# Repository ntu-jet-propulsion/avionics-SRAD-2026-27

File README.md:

TLB_Questions

Question 01:
+5V isolated copper: KiCad is still showing an “isolated copper fill” warning for the +5V zone on In1.Cu. Is this okay to leave, or should I modify/remove the isolated +5V region?

Question 02:
SDA connection: KiCad shows a “copper connection too narrow” warning on the SDA connection, with an effective width of ~0.041 mm even though the track itself is 0.25 mm. Is this something I need to fix, or can it be ignored?

Question 03:
GND vias near J1/J2: KiCad shows drilled-hole clearance warnings because some GND vias are extremely close to the J1/J2 connector PTH holes. Should I move these vias, or is the current placement acceptable?

Question 04:
ESP32 footprint: KiCad reports that the ESP32-C3-WROOM-02 footprint doesn't match the current library footprint. We used the existing/different footprint for the board — is this intentional and okay to keep?

Question 05:
Silkscreen warnings: There are several silkscreen clearance/clipping warnings. Do I need to clean these up before fabrication, or are they acceptable?

Question 06:
Mounting holes: I added two 5 mm NPTH mounting holes. Is their current placement acceptable?

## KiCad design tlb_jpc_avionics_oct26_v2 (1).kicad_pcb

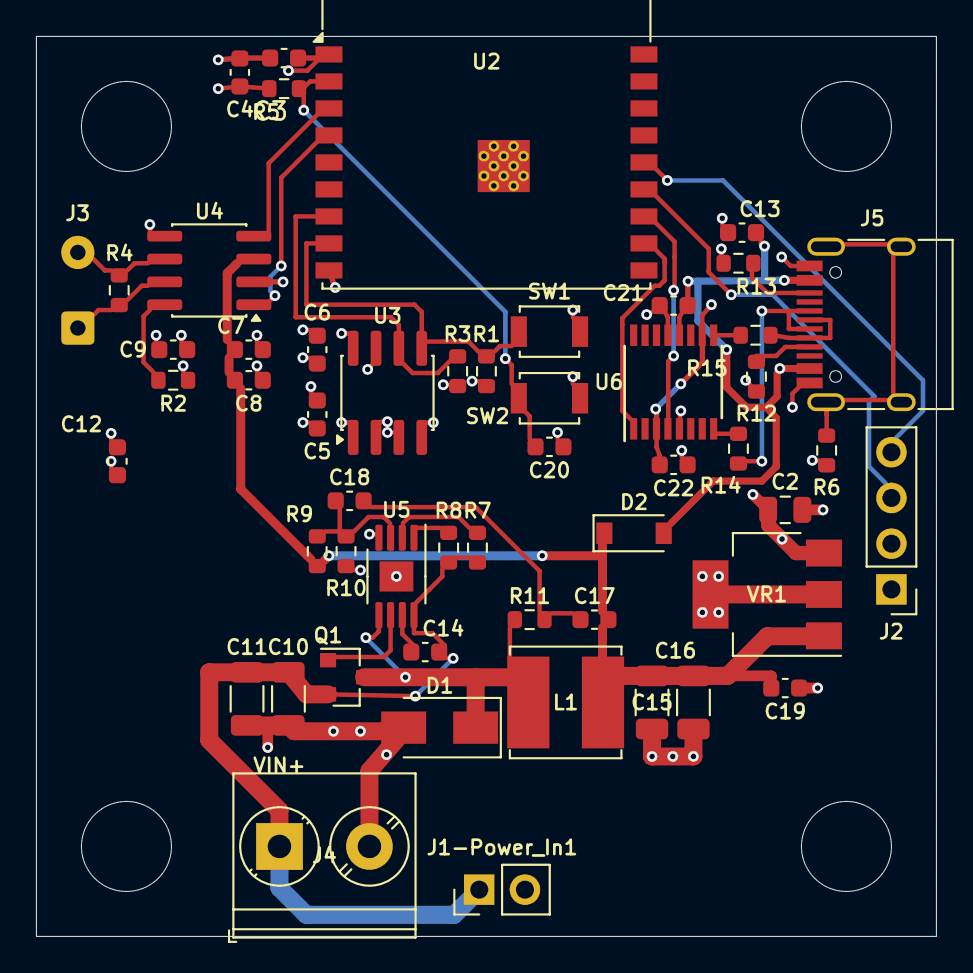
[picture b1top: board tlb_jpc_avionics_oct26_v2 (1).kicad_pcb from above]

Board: 4 copper layers, 50.0 x 50.0 mm, 57 parts (0 on the bottom side), 32 nets.

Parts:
C2: 33u; C_0805_2012Metric
C3, C5, C6, C8, C12: 0.1 uF; C_0603_1608Metric
C4: 10uF; C_0603_1608Metric
C7, C9, C13, C21, C22: 0.1uF; C_0603_1608Metric
C10, C11: 4.7uF 50V; C_1206_3216Metric
C14: 0.47uF 50V; C_0603_1608Metric
C15, C16: 22uF 10V; C_1206_3216Metric
C17: CR (ripple); C_0603_1608Metric
C18: CAC (ripple); C_0603_1608Metric
C19: 0.47uF; C_0603_1608Metric
C20: 1uF; C_0603_1608Metric
D1: SS34 Schottky; D_SMA
D2: B5819W; D_SOD-123
H1, H2, H3, H4: MountingHole_5mm_NPTH; MountingHole_5mm
J1-Power_In1: Conn_01x02; PinHeader_1x02_P2.54mm_Vertical
J2: Light_APRS; PinHeader_1x04_P2.54mm_Vertical
J3: CAN (H,L); SolderWire-0.25sqmm_1x02_P4.2mm_D0.65mm_OD1.7mm
J4: PT1.5/2-5.0-H VIN; TerminalBlock_Phoenix_PT-1,5-2-5.0-H_1x02_P5.00mm_Horizontal
J5: USB-C (HRO TYPE-C-31-M-12); USB_C_Receptacle_HRO_TYPE-C-31-M-12
L1: 15uH SRN6045TA; L_Bourns_SRN6045TA
Q1: PFET -30V (AO3401A); SOT-23-3
R1, R3: 4.7k; R_0603_1608Metric
R2, R5: 10kR; R_0603_1608Metric
R4: 120R; R_0603_1608Metric
R6: 0; R_0603_1608Metric
R7: RT; R_0603_1608Metric
R8: RADJ; R_0603_1608Metric
R9: 3.01k; R_0603_1608Metric
R10: 1.00k; R_0603_1608Metric
R11: RR (ripple); R_0603_1608Metric
R12, R13: 5.1k; R_0603_1608Metric
R14, R15: 27R; R_0603_1608Metric
SW1: BOOT (IO9); SW_SPST_B3U-1000P
SW2: RESET (EN); SW_SPST_B3U-1000P
U2: ESP32-C3; ESP32-C3-WROOM-02
U3: 24LC256; SOIC-8_3.9x4.9mm_P1.27mm
U4: TJA1051TK-3; SOIC-8_3.9x4.9mm_P1.27mm
U5: LM25085MY; MSOP-8-1EP_3x3mm_P0.65mm_EP1.68x1.88mm
U6: FT230XS; SSOP-16_3.9x4.9mm_P0.635mm
VR1: LM3940IMP-3.3; SOT-223-3_TabPin2

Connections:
+3V3: C2.1, C3.2, C4.1, C5.1, C6.1, C9.1, J2.1, R1.1, R3.1, R5.1, U2.1 (3V3), U3.8 (VCC), U4.5 (VIO), VR1.3
+5V: C7.1, C8.2, C15.1, C16.1, C17.2, C19.1, D2.1, L1.2, R9.1, U4.3 (VCC), VR1.1
/APRS_RX: J2.4, U2.14 (IO19)
/APRS_TX: J2.3, U2.13 (IO18)
/BUCK_ADJ: R8.2, U5.1
/BUCK_FB: C18.1, R9.2, R10.2, U5.3
/BUCK_PGATE: Q1.1, U5.6
/BUCK_RIP: C17.1, C18.2, R11.2
/BUCK_RT: R7.2, U5.2
/BUCK_SW: D1.1, L1.1, Q1.3, R11.1, U5.5
/BUCK_VCC: C14.1, U5.7
/CANH: J3.1, R4.1, U4.7 (CANH)
/CANL: J3.2, R4.2, U4.6 (CANL)
/CANRX: U2.3 (IO4), U4.4 (RXD)
/CANTX: U2.4 (IO5), U4.1 (TXD)
/CC1: J5.A5, R12.2
/CC2: J5.B5, R13.2
/FT_3V3: C22.1, U6.3, U6.10
/FT_DM: R15.1, U6.9
/FT_DP: R14.2, U6.8
/SCL: R3.2, U2.7 (IO8), U3.6 (SCL)
/SDA: R1.2, SW1.1, U2.8 (IO9), U3.5 (SDA)
/U0RXD: U2.11 (IO20/RXD), U6.1
/U0TXD: U2.12 (IO21/TXD), U6.4
D+: J5.A6, J5.B6, R14.1
D-: J5.A7, J5.B7, R15.2
GND: C2.2, C3.1, C4.2, C5.2, C6.2, C7.2, C8.1, C9.2, C10.2, C11.2, C12.1, C12.2, C13.1, C15.2, C16.2, C19.2, C20.2, C21.2, C22.2, D1.2, J1-Power_In1.2, J2.2, J4.2, J5.A1, J5.A12, J5.B1, J5.B12, R2.2, R6.2, R10.1, R12.1, R13.1, SW1.2, SW2.2, U2.9 (GND), U2.19 (GND), U3.1 (A0), U3.2 (A1), U3.3 (A2), U3.4 (GND), U3.7 (WP), U4.2 (GND), U5.4, U5.9, U6.5, U6.13, VR1.2
unnamed: J5.S1, R6.1
unnamed: C13.2, C21.1, D2.2, J5.A4, J5.A9, J5.B4, J5.B9, U6.12
unnamed: C20.1, R5.2, SW2.1, U2.2 (EN)
unnamed: R2.1, U4.8 (S)
VIN: C10.1, C11.1, C14.2, J1-Power_In1.1, J4.1, Q1.2, R7.1, R8.1, U5.8

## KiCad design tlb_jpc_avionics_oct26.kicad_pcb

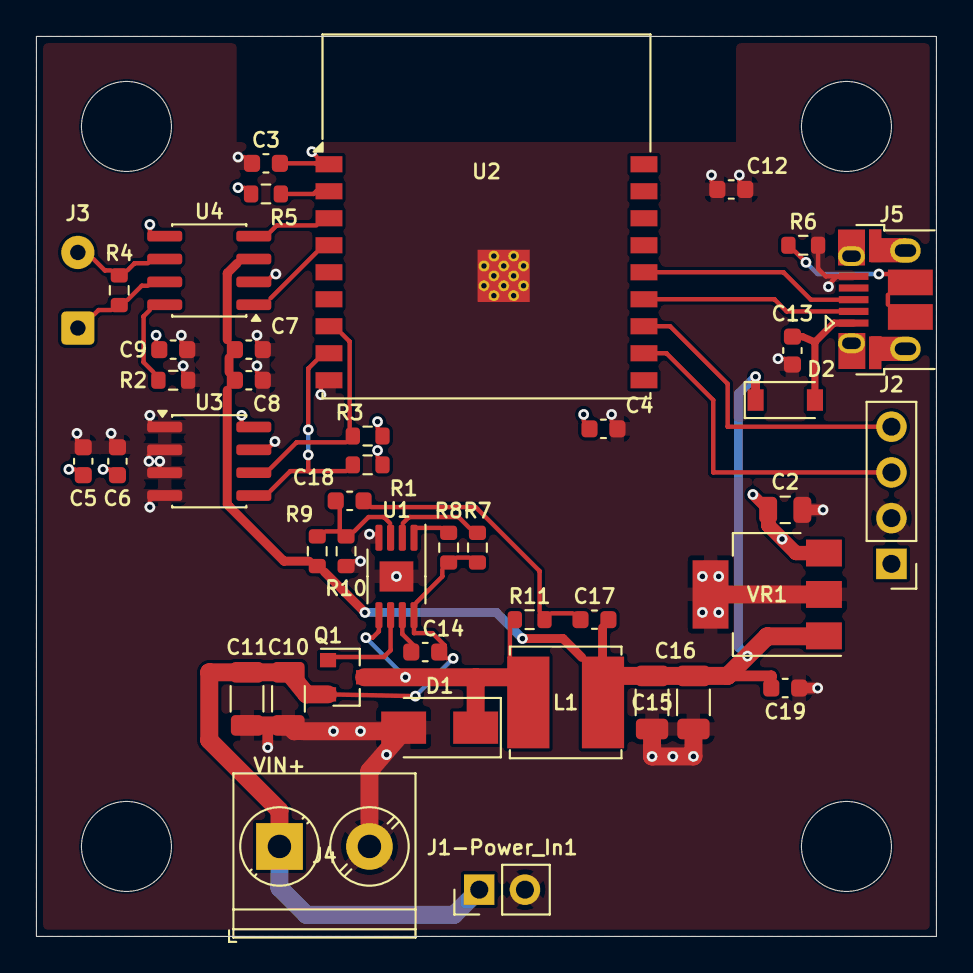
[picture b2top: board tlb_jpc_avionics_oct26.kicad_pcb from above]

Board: 4 copper layers, 50.0 x 50.0 mm, 47 parts (0 on the bottom side), 25 nets.

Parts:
C2: 33u; C_0805_2012Metric
C3, C4, C5, C6, C8, C12: 0.1 uF; C_0603_1608Metric
C7, C9, C13: 0.1uF; C_0603_1608Metric
C10, C11: 4.7uF 50V; C_1206_3216Metric
C14: 0.47uF 50V; C_0603_1608Metric
C15, C16: 22uF 10V; C_1206_3216Metric
C17: CR (ripple); C_0603_1608Metric
C18: CAC (ripple); C_0603_1608Metric
C19: 0.47uF; C_0603_1608Metric
D1: SS34 Schottky; D_SMA
D2: B5819W; D_SOD-123
H1, H2, H3, H4: MountingHole_5mm_NPTH; MountingHole_5mm
J1-Power_In1: Conn_01x02; PinHeader_1x02_P2.54mm_Vertical
J2: Light_APRS; PinHeader_1x04_P2.54mm_Vertical
J3: CAN (H,L); SolderWire-0.25sqmm_1x02_P4.2mm_D0.65mm_OD1.7mm
J4: PT1.5/2-5.0-H VIN; TerminalBlock_Phoenix_PT-1,5-2-5.0-H_1x02_P5.00mm_Horizontal
J5: USB_B_Micro; USB_Micro-B_Amphenol_10103594-0001LF_Horizontal
L1: 15uH SRN6045TA; L_Bourns_SRN6045TA
Q1: PFET -30V (AO3401A); SOT-23-3
R1, R3: 4.7k; R_0603_1608Metric
R2, R5: 10kR; R_0603_1608Metric
R4: 120R; R_0603_1608Metric
R6: 0; R_0603_1608Metric
R7: RT; R_0603_1608Metric
R8: RADJ; R_0603_1608Metric
R9: 3.01k; R_0603_1608Metric
R10: 1.00k; R_0603_1608Metric
R11: RR (ripple); R_0603_1608Metric
U1: LM25085MY; MSOP-8-1EP_3x3mm_P0.65mm_EP1.68x1.88mm
U2: ESP32-C3; ESP32-C3-WROOM-02
U3: 24LC256; SOIC-8_3.9x4.9mm_P1.27mm
U4: TJA1051TK-3; SOIC-8_3.9x4.9mm_P1.27mm
VR1: LM3940IMP-3.3; SOT-223-3_TabPin2

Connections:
+3V3: C2.1, C3.2, C4.1, C5.1, C6.1, C9.1, J2.1, R1.1, R3.1, R5.1, U2.1 (3V3), U3.8 (VCC), U4.5 (VIO), VR1.3
+5V: C7.1, C8.2, C15.1, C16.1, C17.2, C19.1, D2.1, L1.2, R9.1, U4.3 (VCC), VR1.1
/BUCK_ADJ: R8.2, U1.1
/BUCK_FB: C18.1, R9.2, R10.2, U1.3
/BUCK_PGATE: Q1.1, U1.6
/BUCK_RIP: C17.1, C18.2, R11.2
/BUCK_RT: R7.2, U1.2
/BUCK_SW: D1.1, L1.1, Q1.3, R11.1, U1.5
/BUCK_VCC: C14.1, U1.7
/CANH: J3.1, R4.1, U4.7 (CANH)
/CANL: J3.2, R4.2, U4.6 (CANL)
/CANRX: U2.3 (IO4), U4.4 (RXD)
/CANTX: U2.4 (IO5), U4.1 (TXD)
/RX0: J2.4, U2.12 (IO21/TXD)
/SCL: R3.2, U2.7 (IO8), U3.6 (SCL)
/SDA: R1.2, U2.8 (IO9), U3.5 (SDA)
/TX0: J2.3, U2.11 (IO20/RXD)
D+: J5.3 (D+), U2.14 (IO19)
D-: J5.2 (D-), U2.13 (IO18)
GND: C2.2, C3.1, C4.2, C5.2, C6.2, C7.2, C8.1, C9.2, C10.2, C11.2, C12.1, C12.2, C13.1, C15.2, C16.2, C19.2, D1.2, J1-Power_In1.2, J2.2, J4.2, J5.5 (GND), R2.2, R6.2, R10.1, U1.4, U1.9, U2.9 (GND), U2.19 (GND), U3.1 (A0), U3.2 (A1), U3.3 (A2), U3.4 (GND), U3.7 (WP), U4.2 (GND), VR1.2
unnamed: J5.6 (Shield), R6.1
unnamed: C13.2, D2.2, J5.1 (VBUS)
unnamed: R5.2, U2.2 (EN)
unnamed: R2.1, U4.8 (S)
VIN: C10.1, C11.1, C14.2, J1-Power_In1.1, J4.1, Q1.2, R7.1, R8.1, U1.8

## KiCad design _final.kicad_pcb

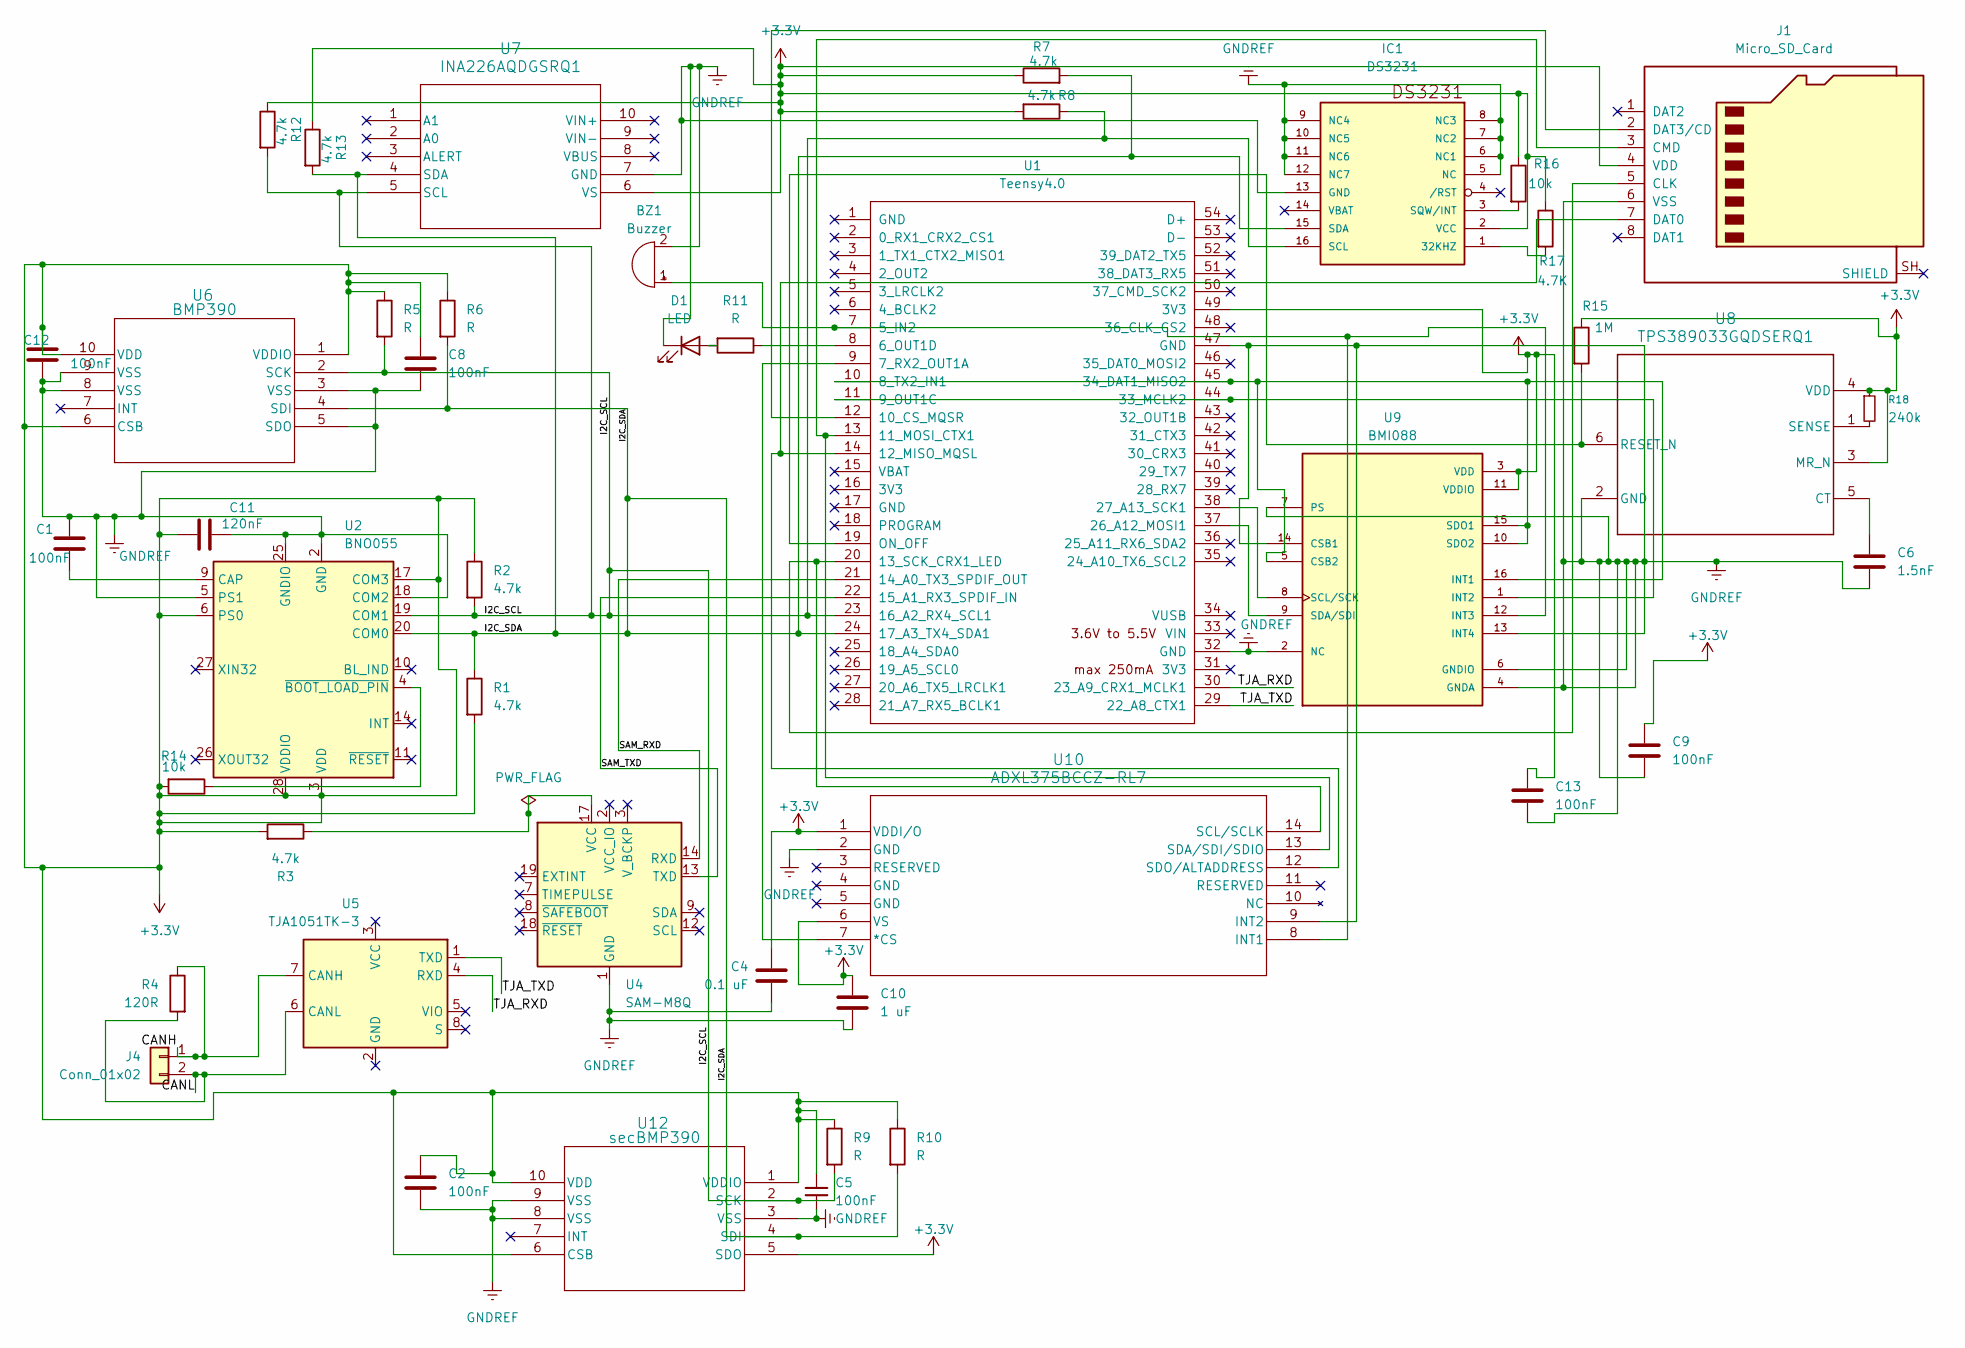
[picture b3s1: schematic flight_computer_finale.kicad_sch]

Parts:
BZ1: Buzzer; Buzzer_12x9.5RM7.6
C1, C2, C5, C8, C9, C12, C13: 100nF; C_01005_0402Metric
C4: 0.1 uF; C_01005_0402Metric
C6: 1.5nF; C_01005_0402Metric
C10: 1 uF; C_01005_0402Metric
C11: 120nF; C_01005_0402Metric
D1: LED; LED_0201_0603Metric
IC1: DS3231; 21-0042B_16_MXM
J1: Micro_SD_Card; microSD_HC_Wuerth_693072010801
J4: Conn_01x02; PinHeader_1x02_P2.54mm_Vertical
R1, R2, R3, R7, R8, R12, R13: 4.7k; R_01005_0402Metric
R4: 120R; R_01005_0402Metric
R5, R6, R9, R10, R11: R; R_01005_0402Metric
R14, R16: 10k; R_01005_0402Metric
R15: 1M; R_01005_0402Metric
R17: 4.7K; R_01005_0402Metric
R18: 240k; R_01005_0402Metric
U1: Teensy4.0; Teensy40_SMT
U2: BNO055; LGA-28_5.2x3.8mm_P0.5mm
U4: SAM-M8Q; ublox_SAM-M8Q
U5: TJA1051TK-3; HVSON-8-1EP_3x3mm_P0.65mm_EP1.6x2.4mm
U6: BMP390; 10LGA_2X2X0p75_BOS
U7: INA226AQDGSRQ1; DGS10_TEX
U8: TPS389033GQDSERQ1; DSE0006A
U9: BMI088; QFN_BMI085_BOS
U10: ADXL375BCCZ-RL7; LGA_CC-14-1_ADI
U12: secBMP390; 10LGA_2X2X0p75_BOS

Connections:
+3.3V: C2.1, C4.1, C5.1, C8.1, C9.1, C10.1, C11.1, C12.1, C13.1, IC1.2 (VCC), J1.4 (VDD), R1.2, R2.1, R3.2, R5.1, R6.1, R7.1, R8.2, R9.1, R10.1, R12.1, R13.1, R14.2, R15.1, R16.1, R17.1, R18.1, U1.49 (3V3), U2.3 (VDD), U2.6 (PS0), U2.17 (COM3), U2.28 (VDDIO), U6.1 (VDDIO), U6.6 (CSB), U6.10 (VDD), U7.6 (VS), U8.3 (MR_N), U8.4 (VDD), U9.3 (VDD), U9.11 (VDDIO), U10.1 (VDDI/O), U10.6 (VS), U12.1 (VDDIO), U12.5 (SDO), U12.6 (CSB), U12.10 (VDD)
/CANH: J4.1, R4.1, U5.7 (CANH)
/CANL: J4.2, R4.2, U5.6 (CANL)
/I2C_SCL: IC1.16 (SCL), R2.2, R5.2, R8.1, R9.2, R12.2, U1.23 (16_A2_RX4_SCL1), U2.19 (COM1), U6.2 (SCK), U7.5 (SCL), U12.2 (SCK)
/I2C_SDA: IC1.15 (SDA), R1.1, R6.2, R7.2, R10.2, R13.2, U1.24 (17_A3_TX4_SDA1), U2.20 (COM0), U6.4 (SDI), U7.4 (SDA), U12.4 (SDI)
/SAM_RXD: U1.21 (14_A0_TX3_SPDIF_OUT), U4.14 (RXD)
/SAM_TXD: U1.22 (15_A1_RX3_SPDIF_IN), U4.13 (TXD)
/TJA_RXD: U1.30 (23_A9_CRX1_MCLK1), U5.4 (RXD)
/TJA_TXD: U1.29 (22_A8_CTX1), U5.1 (TXD)
GNDREF: BZ1.2 (-), C1.1, C2.2, C4.2, C5.2, C6.2, C8.2, C9.2, C10.2, C11.2, C12.2, C13.2, D1.1 (K), IC1.5 (NC), IC1.6 (NC1), IC1.7 (NC2), IC1.8 (NC3), IC1.9 (NC4), IC1.10 (NC5), IC1.11 (NC6), IC1.12 (NC7), IC1.13 (GND), J1.6 (VSS), U1.32 (GND), U1.47 (GND), U2.2 (GND), U2.5 (PS1), U2.18 (COM2), U2.25 (GNDIO), U4.1 (GND), U4.4 (GND), U4.5 (GND), U4.6 (GND), U4.10 (GND), U4.11 (GND), U4.15 (GND), U4.16 (GND), U4.20 (GND), U6.3 (VSS), U6.5 (SDO), U6.8 (VSS), U6.9 (VSS), U7.7 (GND), U8.2 (GND), U9.2 (NC), U9.4 (GNDA), U9.6 (GNDIO), U9.7 (PS), U9.13 (INT4), U9.14 (CSB1), U10.2 (GND), U10.9 (INT2), U12.3 (VSS), U12.8 (VSS), U12.9 (VSS)
unnamed: BZ1.1 (+), U1.7 (5_IN2), U9.12 (INT3), U10.8 (INT1)
unnamed: D1.2 (A), R11.2
unnamed: IC1.1 (32KHZ), R17.2
unnamed: IC1.3 (SQW/INT), R16.2
unnamed: J1.5 (CLK), U1.20 (13_SCK_CRX1_LED), U10.14 (SCL/SCLK)
unnamed: J1.3 (CMD), U1.13 (11_MOSI_CTX1), U10.13 (SDA/SDI/SDIO)
unnamed: J1.7 (DAT0), U1.14 (12_MISO_MQSL), U10.12 (SDO/ALTADDRESS)
unnamed: J1.2 (DAT3/CD), U1.12 (10_CS_MQSR)
unnamed: R11.1, U1.8 (6_OUT1D)
unnamed: U1.9 (7_RX2_OUT1A), U10.7 (*CS)
unnamed: U1.37 (26_A12_MOSI1), U9.9 (SDA/SDI)
unnamed: U1.38 (27_A13_SCK1), U9.8 (SCL/SCK)
unnamed: U1.11 (9_OUT1C), U1.44 (33_MCLK2), U9.1 (INT2)
unnamed: U1.10 (8_TX2_IN1), U1.45 (34_DAT1_MISO2), U9.5 (CSB2), U9.10 (SDO2), U9.15 (SDO1), U9.16 (INT1)
unnamed: R15.2, U1.19 (ON_OFF), U8.6 (RESET_N)
unnamed: C1.2, U2.9 (CAP)
unnamed: R14.1, U2.4 (~BOOT_LOAD_PIN)
unnamed: R3.1, U4.17 (VCC)
unnamed: C6.1, U8.5 (CT)
unnamed: R18.2, U8.1 (SENSE)

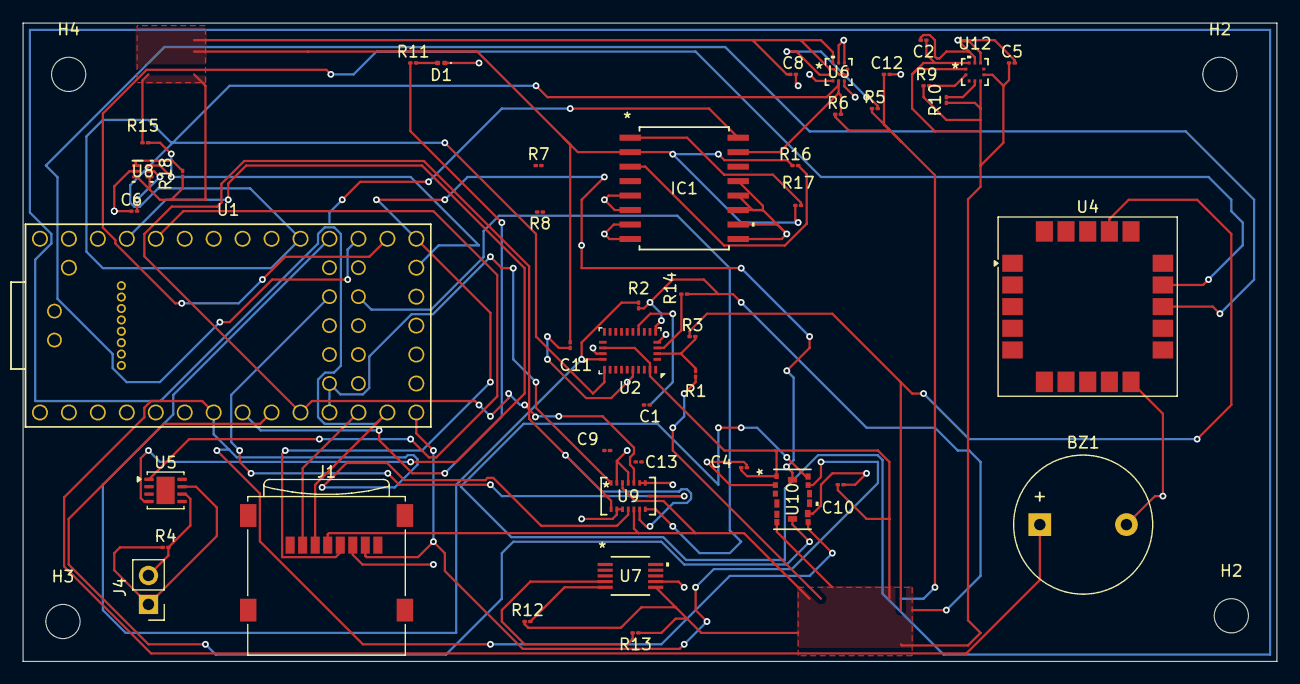
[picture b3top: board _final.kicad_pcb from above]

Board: 4 copper layers, 110.0 x 56.0 mm, 48 parts (0 on the bottom side), 30 nets.

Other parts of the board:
H2, H2#2, H3, H4: MountingHole_3mm

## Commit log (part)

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2026-02-09 Add files via upload
    - managed to debug code for kalman filter and execute Allan variance
    - code still doesn't run properly and pure gibberish is seen in serial plotter along with the error wire.end transmission failed. However, it compiles. Just doesn't plot data or show change in attitu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
